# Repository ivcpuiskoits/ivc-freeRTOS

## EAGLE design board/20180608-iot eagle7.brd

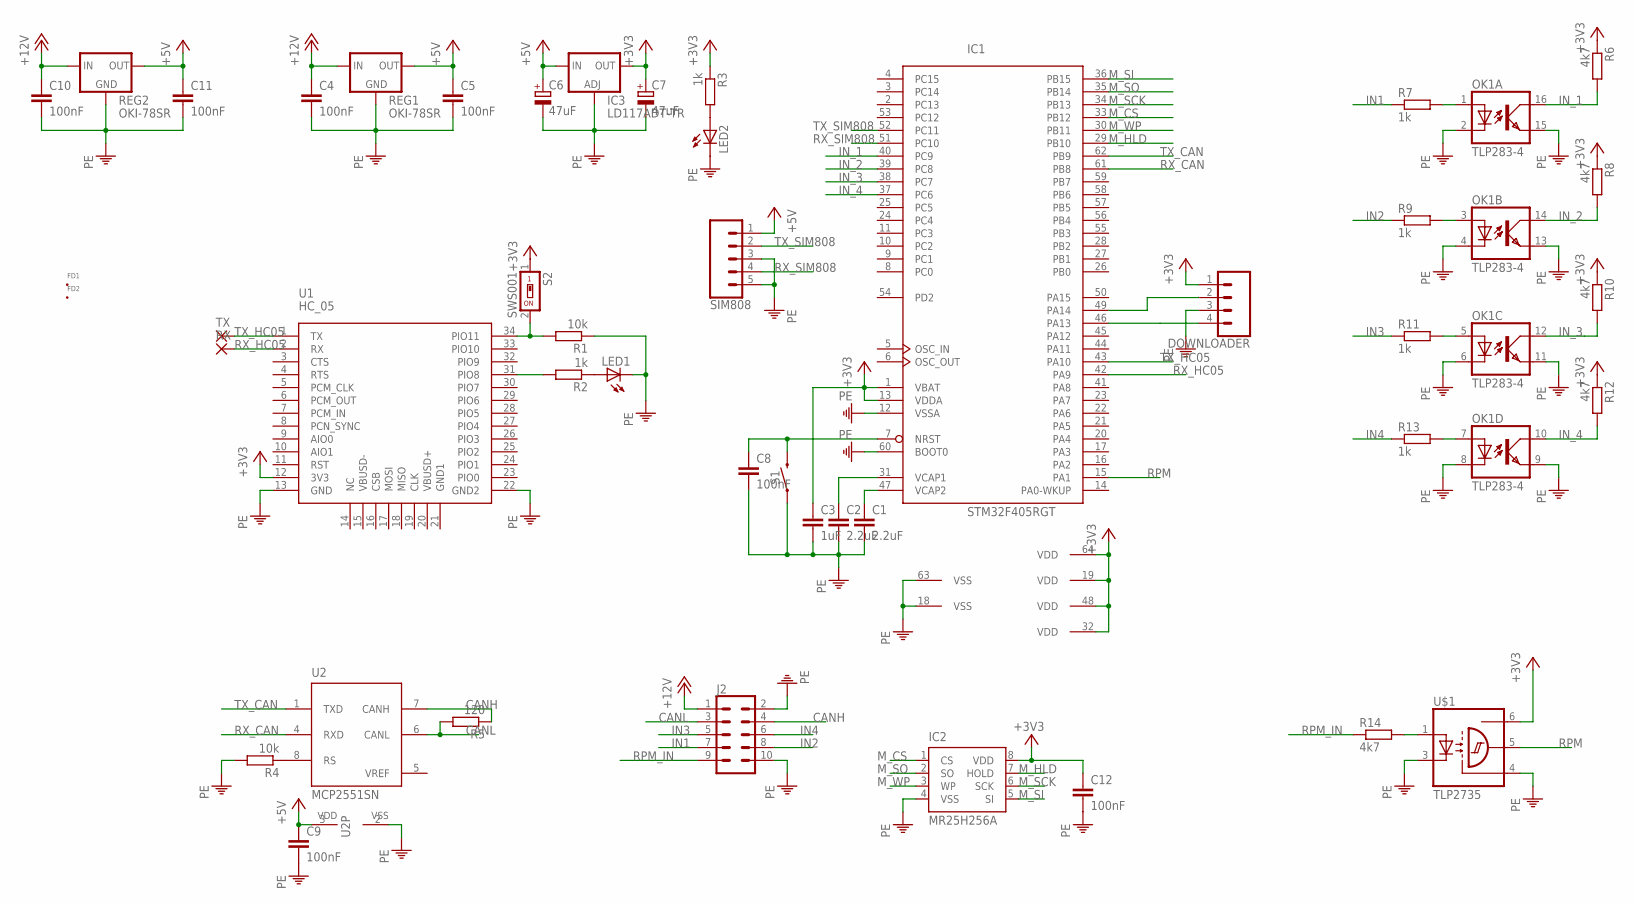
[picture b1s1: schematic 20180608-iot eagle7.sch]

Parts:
C1, C2: 2.2uF; C0805
C3: 1uF; C0805
C4, C5, C8, C9, C10, C11, C12: 100nF; C0805
C6, C7: 47uF; CT7343
DOWNLOADER: CONN_04; 1X04
FD1, FD2: FID_40MIL; FID_040
IC1: STM32F405RGT; LQFP64
IC2: MR25H256A; SON127P600X500X90-9T210
IC3: LD117ADT-TR; DPACK
J2: CONN_05X2; 2X5-EDGE_SMD
LED1, LED2: LEDCHIP-LED0805; CHIP-LED0805
OK1: TLP283-4; MINI-FLAT-16
R1, R4: 10k; R0805
R2, R3, R7, R9, R11, R13: 1k; R0805
R5: 120; R0805
R6, R8, R10, R12, R14: 4k7; R0805
REG1, REG2: OKI-78SR; HDRV3W64P254_1X3_1195X508X838B
RX: SMD2; SMD1,27-2,54
S1: MOMENTARY-SWITCH-SPST-SMD-6.0X3.5MM; TACTILE_SWITCH_SMD_6.0X3.5MM
S2: SWS001; SMS-001
SIM808: CONN_05; 1X05
TX: SMD2; SMD1,27-2,54
U1: HC_05; BLUETOOTH_SMD
U2: MCP2551SN; SO-08
U$1: TLP2735; SOIC127P1000X210-6

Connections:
+3V3: C3.1, C7.+, C12.1, DOWNLOADER.1, IC1.1 (VBAT), IC1.13 (VDDA), IC1.19 (VDD), IC1.32 (VDD), IC1.48 (VDD), IC1.64 (VDD), IC2.8 (VDD), IC3.4 (OUT), R3.1, R6.1, R8.1, R10.1, R12.1, S2.1, U1.12 (3V3), U$1.6 (VCC)
+5V: C5.1, C6.+, C9.1, C11.1, IC3.3 (IN), REG1.3 (OUT), REG2.3 (OUT), SIM808.1, U2.3 (VDD)
+12V: C4.1, C10.1, J2.1, REG1.1 (IN), REG2.1 (IN)
CANH: J2.4, R5.1, U2.7 (CANH)
CANL: J2.3, R5.2, U2.6 (CANL)
IN1: J2.7, R7.1
IN2: J2.8, R9.1
IN3: J2.5, R11.1
IN4: J2.6, R13.1
IN_1: IC1.40 (PC9), OK1.16 (COL), R6.2
IN_2: IC1.39 (PC8), OK1.14 (COL), R8.2
IN_3: IC1.38 (PC7), OK1.12 (COL), R10.2
IN_4: IC1.37 (PC6), OK1.10 (COL), R12.2
M_CS: IC1.33 (PB12), IC2.1 (CS)
M_HLD: IC1.29 (PB10), IC2.7 (HOLD)
M_SCK: IC1.34 (PB13), IC2.6 (SCK)
M_SI: IC1.36 (PB15), IC2.5 (SI)
M_SO: IC1.35 (PB14), IC2.2 (SO)
M_WP: IC1.30 (PB11), IC2.3 (WP)
unnamed: DOWNLOADER.2, IC1.49 (PA14)
unnamed: DOWNLOADER.4, IC1.46 (PA13)
unnamed: C1.1, IC1.47 (VCAP2)
unnamed: C2.1, IC1.31 (VCAP1)
unnamed: C8.1, IC1.7 (NRST), S1.2
unnamed: LED1.A, R2.1
unnamed: R1.2, S2.2, U1.34 (PIO11)
unnamed: R2.2, U1.31 (PIO8)
unnamed: LED2.A, R3.2
unnamed: R4.1, U2.8 (RS)
unnamed: OK1.1 (A), R7.2
unnamed: R14.2, U$1.1 (A)
unnamed: OK1.3 (A), R9.2
unnamed: OK1.5 (A), R11.2
unnamed: OK1.7 (A), R13.2
PE: C1.2, C2.2, C3.2, C4.2, C5.2, C6.-, C7.-, C8.2, C9.2, C10.2, C11.2, C12.2, DOWNLOADER.3, IC1.12 (VSSA), IC1.18 (VSS), IC1.60 (BOOT0), IC1.63 (VSS), IC2.4 (VSS), IC3.1 (ADJ), J2.2, J2.10, LED1.C, LED2.C, OK1.2 (C), OK1.4 (C), OK1.6 (C), OK1.8 (C), OK1.9 (EMIT), OK1.11 (EMIT), OK1.13 (EMIT), OK1.15 (EMIT), R1.1, R4.2, REG1.2 (GND), REG2.2 (GND), S1.1, SIM808.3, SIM808.5, U1.13 (GND), U1.22 (GND2), U2.2 (VSS), U$1.3 (C), U$1.4 (GND)
RPM: IC1.15 (PA1), U$1.5 (OUT)
RPM_IN: J2.9, R14.1
RX_CAN: IC1.61 (PB8), U2.4 (RXD)
RX_HC05: IC1.42 (PA9), RX.1, U1.2 (RX)
RX_SIM808: IC1.51 (PC10), SIM808.4
TX_CAN: IC1.62 (PB9), U2.1 (TXD)
TX_HC05: IC1.43 (PA10), TX.1, U1.1 (TX)
TX_SIM808: IC1.52 (PC11), SIM808.2
VREF: U2.5 (VREF)

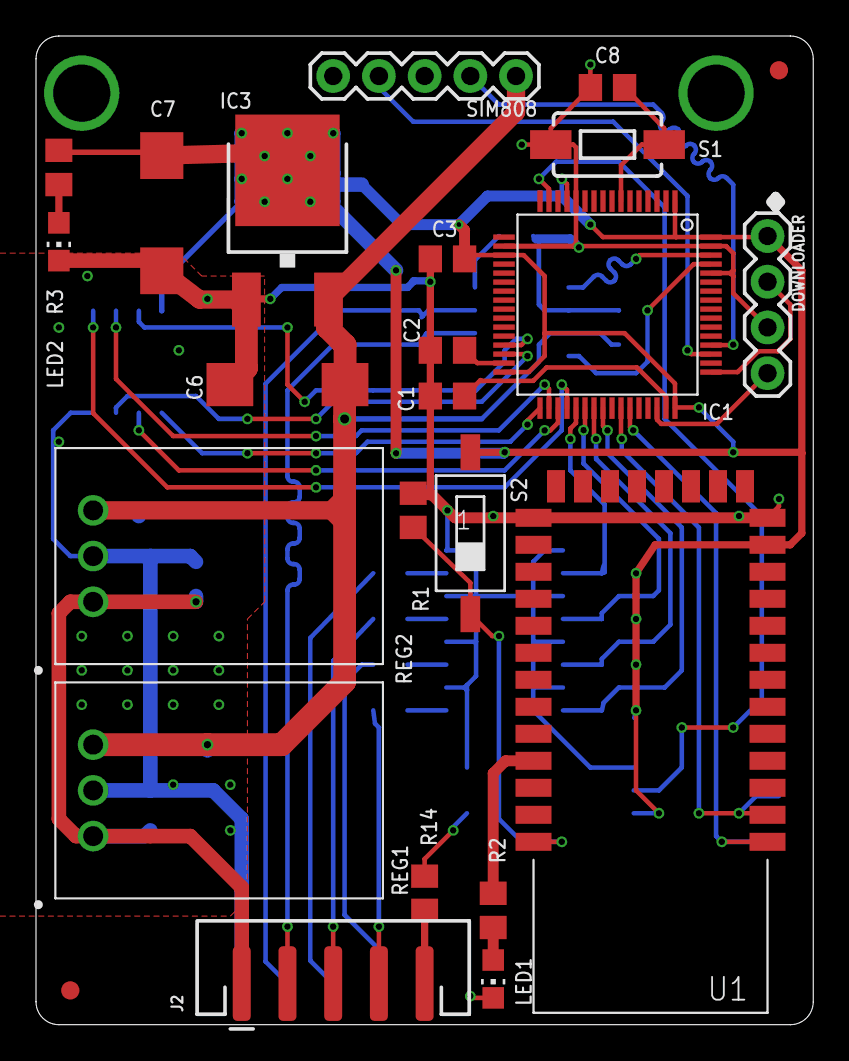
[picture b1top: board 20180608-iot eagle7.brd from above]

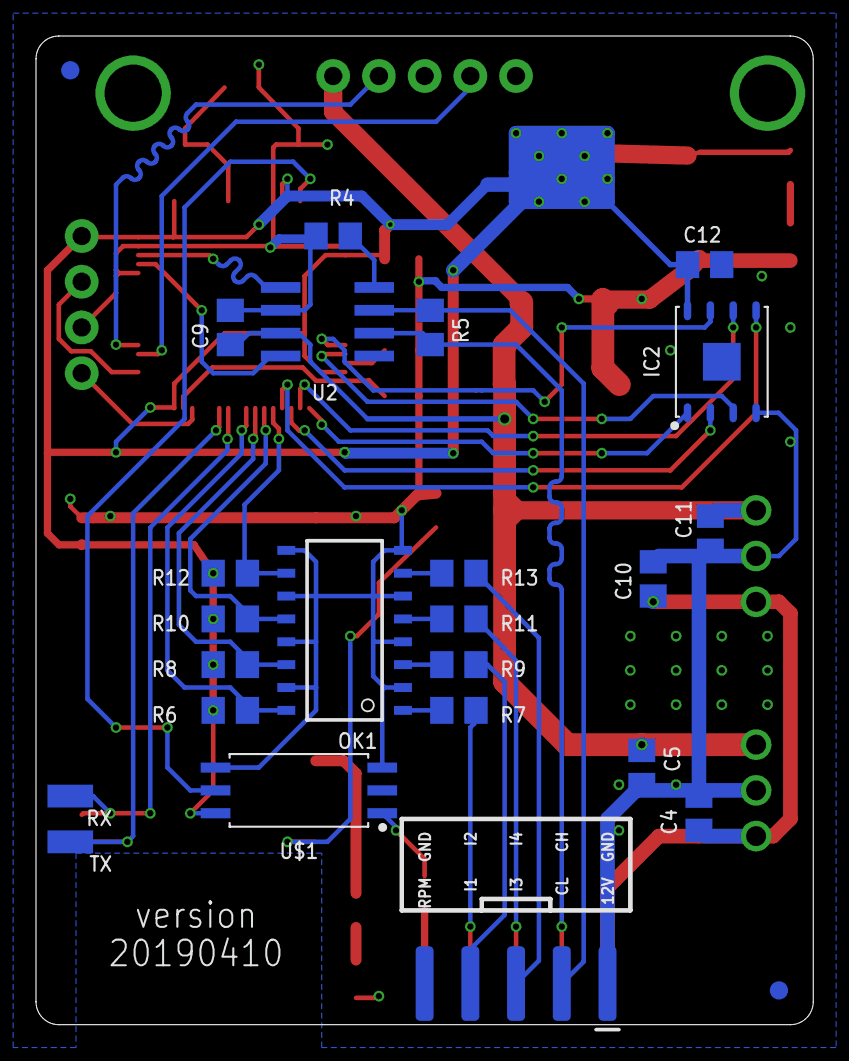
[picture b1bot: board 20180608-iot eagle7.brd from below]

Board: 2 copper layers, 43.2 x 54.9 mm, 46 parts (22 on the bottom side), 43 nets.

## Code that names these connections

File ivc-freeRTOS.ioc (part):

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Mcu.Name=STM32F405RGTx
Mcu.Package=LQFP64
Mcu.UserName=STM32F405RGTx
PA1.Signal=GPXTI1
PA10.Mode=Asynchronous
PA10.Signal=USART1_RX
PA13.Mode=Serial_Wire
PA13.Signal=SYS_JTMS-SWDIO
PA14.Mode=Serial_Wire
PA14.Signal=SYS_JTCK-SWCLK
PA9.Mode=Asynchronous
PA9.Signal=USART1_TX
PB10.Signal=GPIO_Output
PB11.Signal=GPIO_Output
PB12.Signal=SPI2_NSS
PB13.Signal=SPI2_SCK
PB14.Signal=SPI2_MISO
PB15.Signal=SPI2_MOSI
PB8.Mode=Master
PB8.Signal=CAN1_RX
PB9.Mode=Master
PB9.Signal=CAN1_TX
PC10.Mode=Asynchronous
PC10.Signal=USART3_TX
PC11.Mode=Asynchronous
PC11.Signal=USART3_RX
PC6.GPIOParameters=GPIO_Label
PC6.GPIO_Label=IN4
PC6.Signal=GPIO_Input
PC7.GPIOParameters=GPIO_Label
PC7.GPIO_Label=IN3
PC7.Signal=GPIO_Input
PC8.GPIOParameters=GPIO_Label
PC8.GPIO_Label=IN2
PC8.Signal=GPIO_Input
PC9.GPIOParameters=GPIO_Label
PC9.GPIO_Label=IN1
PC9.Signal=GPIO_Input
RCC.HSE_VALUE=25000000
RCC.SYSCLKFreq_VALUE=168000000
RCC.SYSCLKSource=RCC_SYSCLKSOURCE_PLLCLK
board=custom

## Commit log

2019-03-11 add gsmStatus()
2019-07-03 add board
2019-07-03 add board eagle v7

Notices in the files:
parts and their libraries:
SparkFun-Connectors: Licensing: Creative Commons ShareAlike 4.0 International - https://creativecommons.org/licenses/by-sa/4.0
